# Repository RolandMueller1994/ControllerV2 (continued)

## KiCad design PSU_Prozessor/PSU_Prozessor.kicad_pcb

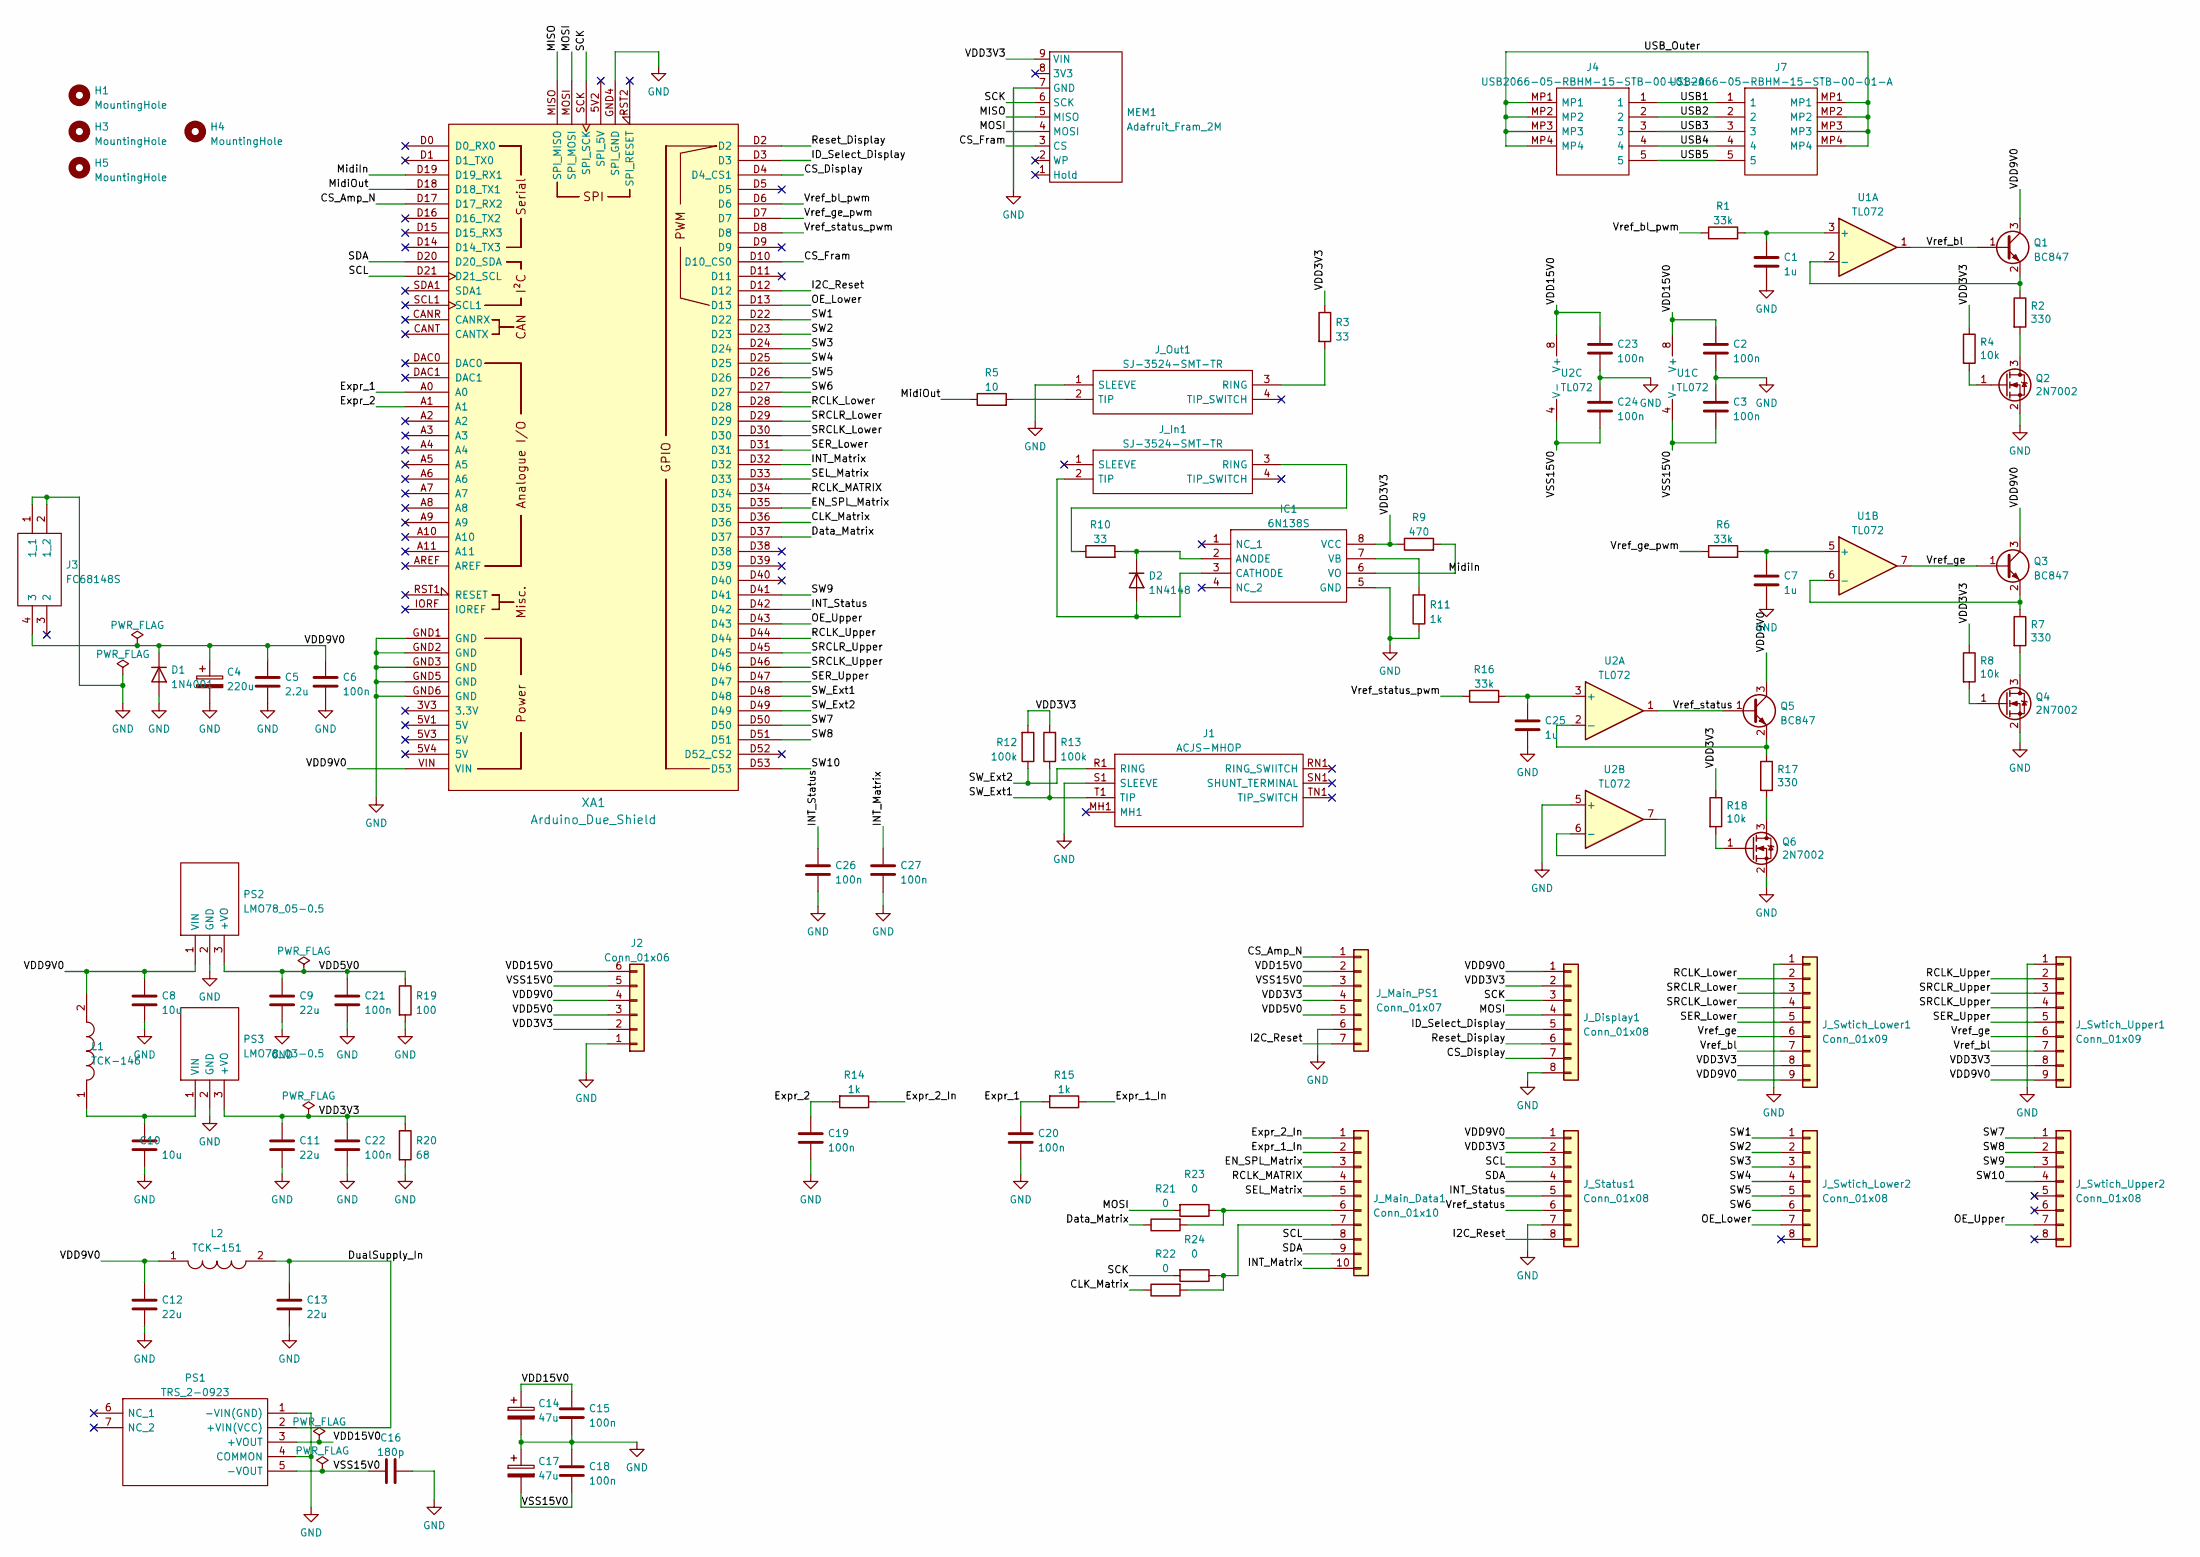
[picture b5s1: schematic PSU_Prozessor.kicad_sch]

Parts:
C1, C7, C25: 1u; C_1206_3216Metric_Pad1.33x1.80mm_HandSolder
C2, C3, C6, C15, C18, C19, C20, C21, C22, C23, C24, C26, C27: 100n; C_1206_3216Metric_Pad1.33x1.80mm_HandSolder
C4: 220u; CP_Elec_10x10
C5: 2.2u; C_1206_3216Metric_Pad1.33x1.80mm_HandSolder
C8, C10: 10u; C_1206_3216Metric_Pad1.33x1.80mm_HandSolder
C9, C11, C12, C13: 22u; C_1206_3216Metric_Pad1.33x1.80mm_HandSolder
C14, C17: 47u; CP_Elec_8x10.5
C16: 180p; C_1206_3216Metric_Pad1.33x1.80mm_HandSolder
D1: 1N4001; D_DO-41_SOD81_P10.16mm_Horizontal
D2: 1N4148; D_DO-35_SOD27_P7.62mm_Horizontal
H1, H3, H4, H5: MountingHole; MountingHole_4mm
IC1: 6N138S; SOP254P1016X460-8N; Manufacturer_Part_Number 6N138S; Mouser Part Number 859-6N138S
J1: ACJS-MHOP; ACJSMHOP; Manufacturer_Part_Number ACJS-MHOP; Mouser Part Number 523-ACJS-MHOP
J2: Conn_01x06; PinHeader_1x06_P2.54mm_Vertical
J3: FC68148S; FC68148S_2; Manufacturer_Part_Number FC68148S
J4, J7: USB2066-05-RBHM-15-STB-00-01-A; USB206605RBHM15STB0001A; Manufacturer_Part_Number USB2066-05-RBHM-15-STB-00-01-A; Mouser Part Number 640-2665RBHM15STB01A
J_Display1: Conn_01x08; JST_PH_B8B-PH-K_1x08_P2.00mm_Vertical
J_In1: SJ-3524-SMT-TR; Manufacturer_Part_Number SJ-3524-SMT-TR; Mouser Part Number 490-SJ-3524-SMT-TR
J_Main_Data1: Conn_01x10; JST_PH_B10B-PH-K_1x10_P2.00mm_Vertical
J_Main_PS1: Conn_01x07; JST_PH_B7B-PH-K_1x07_P2.00mm_Vertical
J_Out1: SJ-3524-SMT-TR; Manufacturer_Part_Number SJ-3524-SMT-TR; Mouser Part Number 490-SJ-3524-SMT-TR
J_Status1: Conn_01x08; JST_PH_B8B-PH-K_1x08_P2.00mm_Vertical
J_Swtich_Lower1: Conn_01x09; JST_PH_B9B-PH-K_1x09_P2.00mm_Vertical
J_Swtich_Lower2: Conn_01x08; JST_PH_B8B-PH-K_1x08_P2.00mm_Vertical
J_Swtich_Upper1: Conn_01x09; JST_PH_B9B-PH-K_1x09_P2.00mm_Vertical
J_Swtich_Upper2: Conn_01x08; JST_PH_B8B-PH-K_1x08_P2.00mm_Vertical
L1: TCK-146; TCK147; Manufacturer_Part_Number TCK-146; Mouser Part Number 495-TCK-146
L2: TCK-151; TCK151; Manufacturer_Part_Number TCK-151; Mouser Part Number 495-TCK-151
MEM1: Adafruit_Fram_2M; Adafruit_FRam_2M
PS1: TRS_2-0923; TRS20922; Manufacturer_Part_Number TRS 2-0923; Mouser Part Number 495-TRS2-0923
PS2: LMO78_05-0.5; LMO78_0505; Manufacturer_Part_Number LMO78_05-0.5
PS3: LMO78_03-0.5; LMO78_0505; Manufacturer_Part_Number LMO78_05-0.5
Q1, Q3, Q5: BC847; SOT-23
Q2, Q4, Q6: 2N7002; SOT-23
R1, R6, R16: 33k; R_1206_3216Metric_Pad1.30x1.75mm_HandSolder
R2, R7, R17: 330; R_1206_3216Metric_Pad1.30x1.75mm_HandSolder
R3, R10: 33; R_1206_3216Metric_Pad1.30x1.75mm_HandSolder
R4, R8, R18: 10k; R_1206_3216Metric_Pad1.30x1.75mm_HandSolder
R5: 10; R_1206_3216Metric_Pad1.30x1.75mm_HandSolder
R9: 470; R_1206_3216Metric_Pad1.30x1.75mm_HandSolder
R11, R14, R15: 1k; R_1206_3216Metric_Pad1.30x1.75mm_HandSolder
R12, R13: 100k; R_1206_3216Metric_Pad1.30x1.75mm_HandSolder
R19: 100; R_Axial_DIN0414_L11.9mm_D4.5mm_P15.24mm_Horizontal
R20: 68; R_Axial_DIN0414_L11.9mm_D4.5mm_P15.24mm_Horizontal
R21, R22, R23, R24: 0; R_1206_3216Metric_Pad1.30x1.75mm_HandSolder
U1, U2: TL072; SOIC127P600X175-8N
XA1: Arduino_Due_Shield

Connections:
/CLK_Matrix: R22.1, XA1.D36
/CS_Amp_N: J_Main_PS1.1, XA1.D17 (D17_RX2)
/CS_Display: J_Display1.7, XA1.D4 (D4_CS1)
/CS_Fram: MEM1.3 (CS), XA1.D10 (D10_CS0)
/Data_Matrix: R21.1, XA1.D37
/DualSupply_In: C13.1, L2.2, PS1.2 (+VIN(VCC))
/EN_SPL_Matrix: J_Main_Data1.3, XA1.D35
/Expr_1: C20.1, R15.2, XA1.A0
/Expr_1_In: J_Main_Data1.2, R15.1
/Expr_2: C19.1, R14.2, XA1.A1
/Expr_2_In: J_Main_Data1.1, R14.1
/I2C_Reset: J_Main_PS1.7, J_Status1.8, XA1.D12
/ID_Select_Display: J_Display1.5, XA1.D3
/INT_Matrix: C27.1, J_Main_Data1.10, XA1.D32
/INT_Status: C26.1, J_Status1.5, XA1.D42
/MISO: MEM1.5 (MISO), XA1.MISO (SPI_MISO)
/MOSI: J_Display1.4, MEM1.4 (MOSI), R23.2, XA1.MOSI (SPI_MOSI)
/MidiIn: IC1.6 (VO), R9.2, XA1.D19 (D19_RX1)
/MidiOut: R5.1, XA1.D18 (D18_TX1)
/OE_Lower: J_Swtich_Lower2.7, XA1.D13
/OE_Upper: J_Swtich_Upper2.7, XA1.D43
/RCLK_Lower: J_Swtich_Lower1.2, XA1.D28
/RCLK_MATRIX: J_Main_Data1.4, XA1.D34
/RCLK_Upper: J_Swtich_Upper1.2, XA1.D44
/Reset_Display: J_Display1.6, XA1.D2
/SCK: J_Display1.3, MEM1.6 (SCK), R24.2, XA1.SCK (SPI_SCK)
/SCL: J_Main_Data1.8, J_Status1.3, XA1.D21 (D21_SCL)
/SDA: J_Main_Data1.9, J_Status1.4, XA1.D20 (D20_SDA)
/SEL_Matrix: J_Main_Data1.5, XA1.D33
/SER_Lower: J_Swtich_Lower1.5, XA1.D31
/SER_Upper: J_Swtich_Upper1.5, XA1.D47
/SRCLK_Lower: J_Swtich_Lower1.4, XA1.D30
/SRCLK_Upper: J_Swtich_Upper1.4, XA1.D46
/SRCLR_Lower: J_Swtich_Lower1.3, XA1.D29
/SRCLR_Upper: J_Swtich_Upper1.3, XA1.D45
/SW1: J_Swtich_Lower2.1, XA1.D22
/SW2: J_Swtich_Lower2.2, XA1.D23
/SW3: J_Swtich_Lower2.3, XA1.D24
/SW4: J_Swtich_Lower2.4, XA1.D25
/SW5: J_Swtich_Lower2.5, XA1.D26
/SW6: J_Swtich_Lower2.6, XA1.D27
/SW7: J_Swtich_Upper2.1, XA1.D50
/SW8: J_Swtich_Upper2.2, XA1.D51
/SW9: J_Swtich_Upper2.3, XA1.D41
/SW10: J_Swtich_Upper2.4, XA1.D53
/SW_Ext1: J1.T1 (TIP), R13.1, XA1.D48
/SW_Ext2: J1.R1 (RING), R12.1, XA1.D49
/USB1: J4.1, J7.1
/USB2: J4.2, J7.2
/USB3: J4.3, J7.3
/USB4: J4.4, J7.4
/USB5: J4.5, J7.5
/USB_Outer: J4.MP1, J4.MP2, J4.MP3, J4.MP4, J7.MP1, J7.MP2, J7.MP3, J7.MP4
/VDD3V3: C11.1, C22.1, IC1.8 (VCC), J2.2, J_Display1.2, J_Main_PS1.4, J_Status1.2, J_Swtich_Lower1.8, J_Swtich_Upper1.8, MEM1.9 (VIN), PS3.3 (+VO), R3.1, R4.1, R8.1, R9.1, R12.2, R13.2, R18.1, R20.1
/VDD5V0: C9.1, C21.1, J2.3, J_Main_PS1.5, PS2.3 (+VO), R19.1
/VDD9V0: C4.1, C5.1, C6.1, C8.1, C12.1, D1.1 (K), J2.4, J3.4 (3), J_Display1.1, J_Status1.1, J_Swtich_Lower1.9, J_Swtich_Upper1.9, L1.2, L2.1, PS2.1 (VIN), Q1.3 (C), Q3.3 (C), Q5.3 (C), XA1.VIN
/VDD15V0: C2.1, C14.1, C15.1, C23.1, J2.6, J_Main_PS1.2, PS1.3 (+VOUT), U1.8 (V+), U2.8 (V+)
/VSS15V0: C3.2, C16.1, C17.2, C18.2, C24.2, J2.5, J_Main_PS1.3, PS1.5 (-VOUT), U1.4 (V-), U2.4 (V-)
/Vref_bl: J_Swtich_Lower1.7, J_Swtich_Upper1.7, Q1.1 (B), U1.1
/Vref_bl_pwm: R1.1, XA1.D6
/Vref_ge: J_Swtich_Lower1.6, J_Swtich_Upper1.6, Q3.1 (B), U1.7
/Vref_ge_pwm: R6.1, XA1.D7
/Vref_status: J_Status1.6, Q5.1 (B), U2.1
/Vref_status_pwm: R16.1, XA1.D8
GND: C1.2, C2.2, C3.1, C4.2, C5.2, C6.2, C7.2, C8.2, C9.2, C10.2, C11.2, C12.2, C13.2, C14.2, C15.2, C16.2, C17.1, C18.1, C19.2, C20.2, C21.2, C22.2, C23.2, C24.1, C25.2, C26.2, C27.2, D1.2 (A), IC1.5 (GND), J1.S1 (SLEEVE), J2.1, J3.1 (1_1), J3.2 (1_2), J_Display1.8, J_Main_PS1.6, J_Out1.1 (SLEEVE), J_Status1.7, J_Swtich_Lower1.1, J_Swtich_Upper1.1, MEM1.7 (GND), PS1.1 (-VIN(GND)), PS1.4 (COMMON), PS2.2 (GND), PS3.2 (GND), Q2.2 (S), Q4.2 (S), Q6.2 (S), R11.1, R19.2, R20.2, U2.5 (+), XA1.GND1 (GND), XA1.GND2 (GND), XA1.GND3 (GND), XA1.GND4 (SPI_GND), XA1.GND5 (GND), XA1.GND6 (GND)
unnamed: C1.1, R1.2, U1.3 (+)
unnamed: C7.1, R6.2, U1.5 (+)
unnamed: C10.1, L1.1, PS3.1 (VIN)
unnamed: C25.1, R16.2, U2.3 (+)
unnamed: D2.1 (K), IC1.2 (ANODE), R10.2
unnamed: D2.2 (A), IC1.3 (CATHODE), J_In1.2 (TIP)
unnamed: IC1.7 (VB), R11.2
unnamed: J_In1.3 (RING), R10.1
unnamed: J_Main_Data1.6, R21.2, R23.1
unnamed: J_Main_Data1.7, R22.2, R24.1
unnamed: J_Out1.2 (TIP), R5.2
unnamed: J_Out1.3 (RING), R3.2
unnamed: Q1.2 (E), R2.1, U1.2 (-)
unnamed: Q2.1 (G), R4.2
unnamed: Q2.3 (D), R2.2
unnamed: Q3.2 (E), R7.1, U1.6 (-)
unnamed: Q4.1 (G), R8.2
unnamed: Q4.3 (D), R7.2
unnamed: Q5.2 (E), R17.1, U2.2 (-)
unnamed: Q6.1 (G), R18.2
unnamed: Q6.3 (D), R17.2
unnamed: U2.6 (-), U2.7

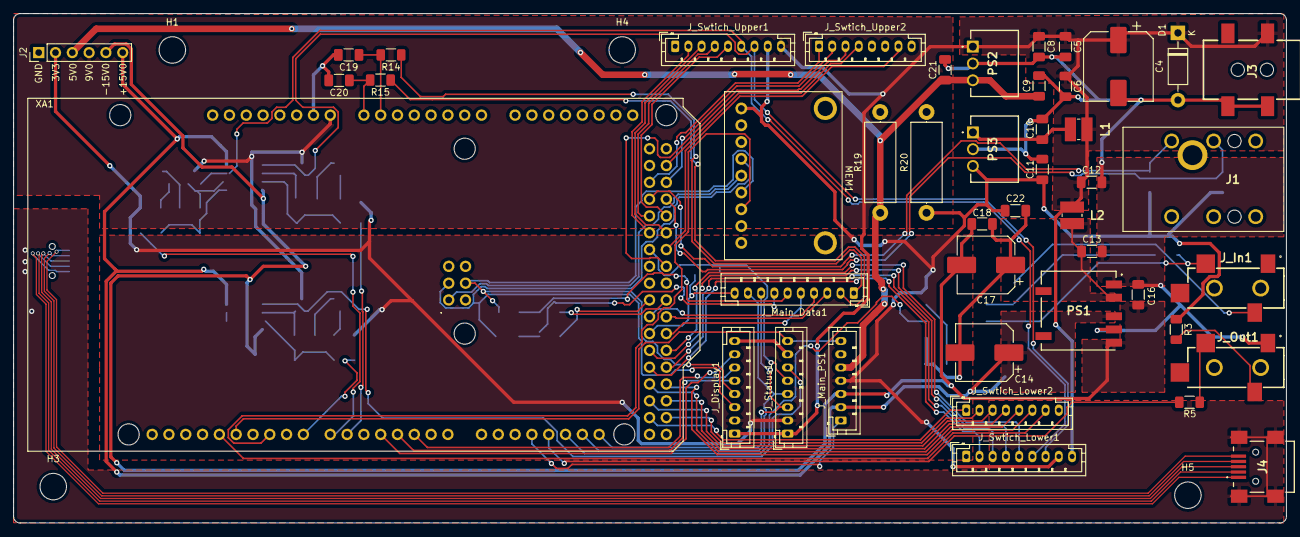
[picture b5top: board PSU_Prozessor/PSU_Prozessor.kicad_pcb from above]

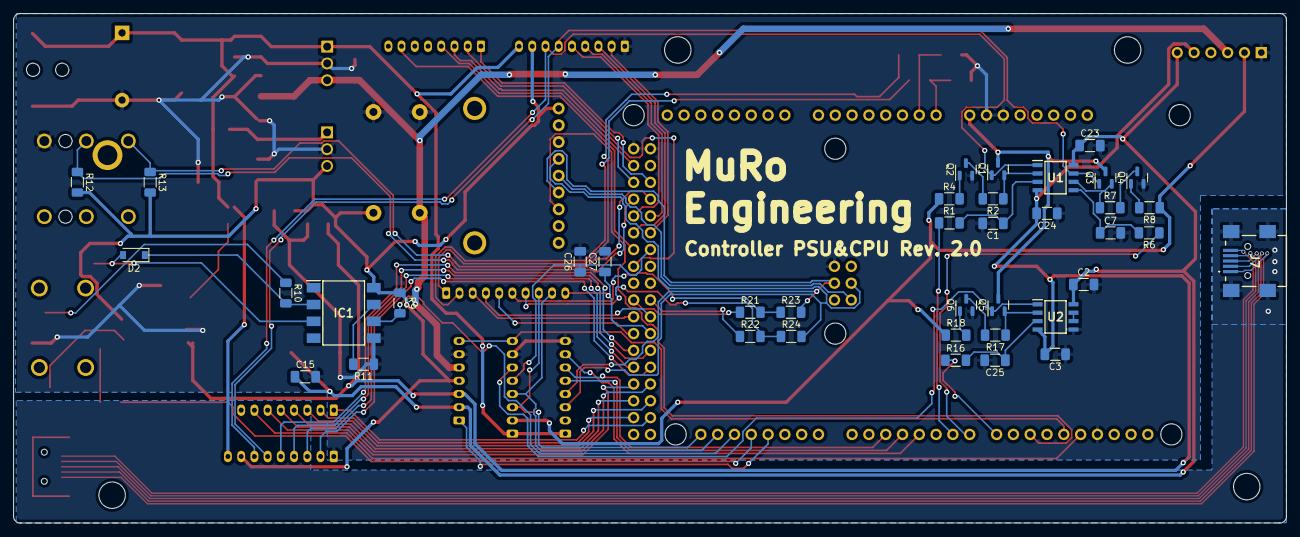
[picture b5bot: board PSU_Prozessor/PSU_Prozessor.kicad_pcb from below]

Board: 2 copper layers, 192.4 x 77.0 mm, 88 parts (39 on the bottom side), 87 nets.

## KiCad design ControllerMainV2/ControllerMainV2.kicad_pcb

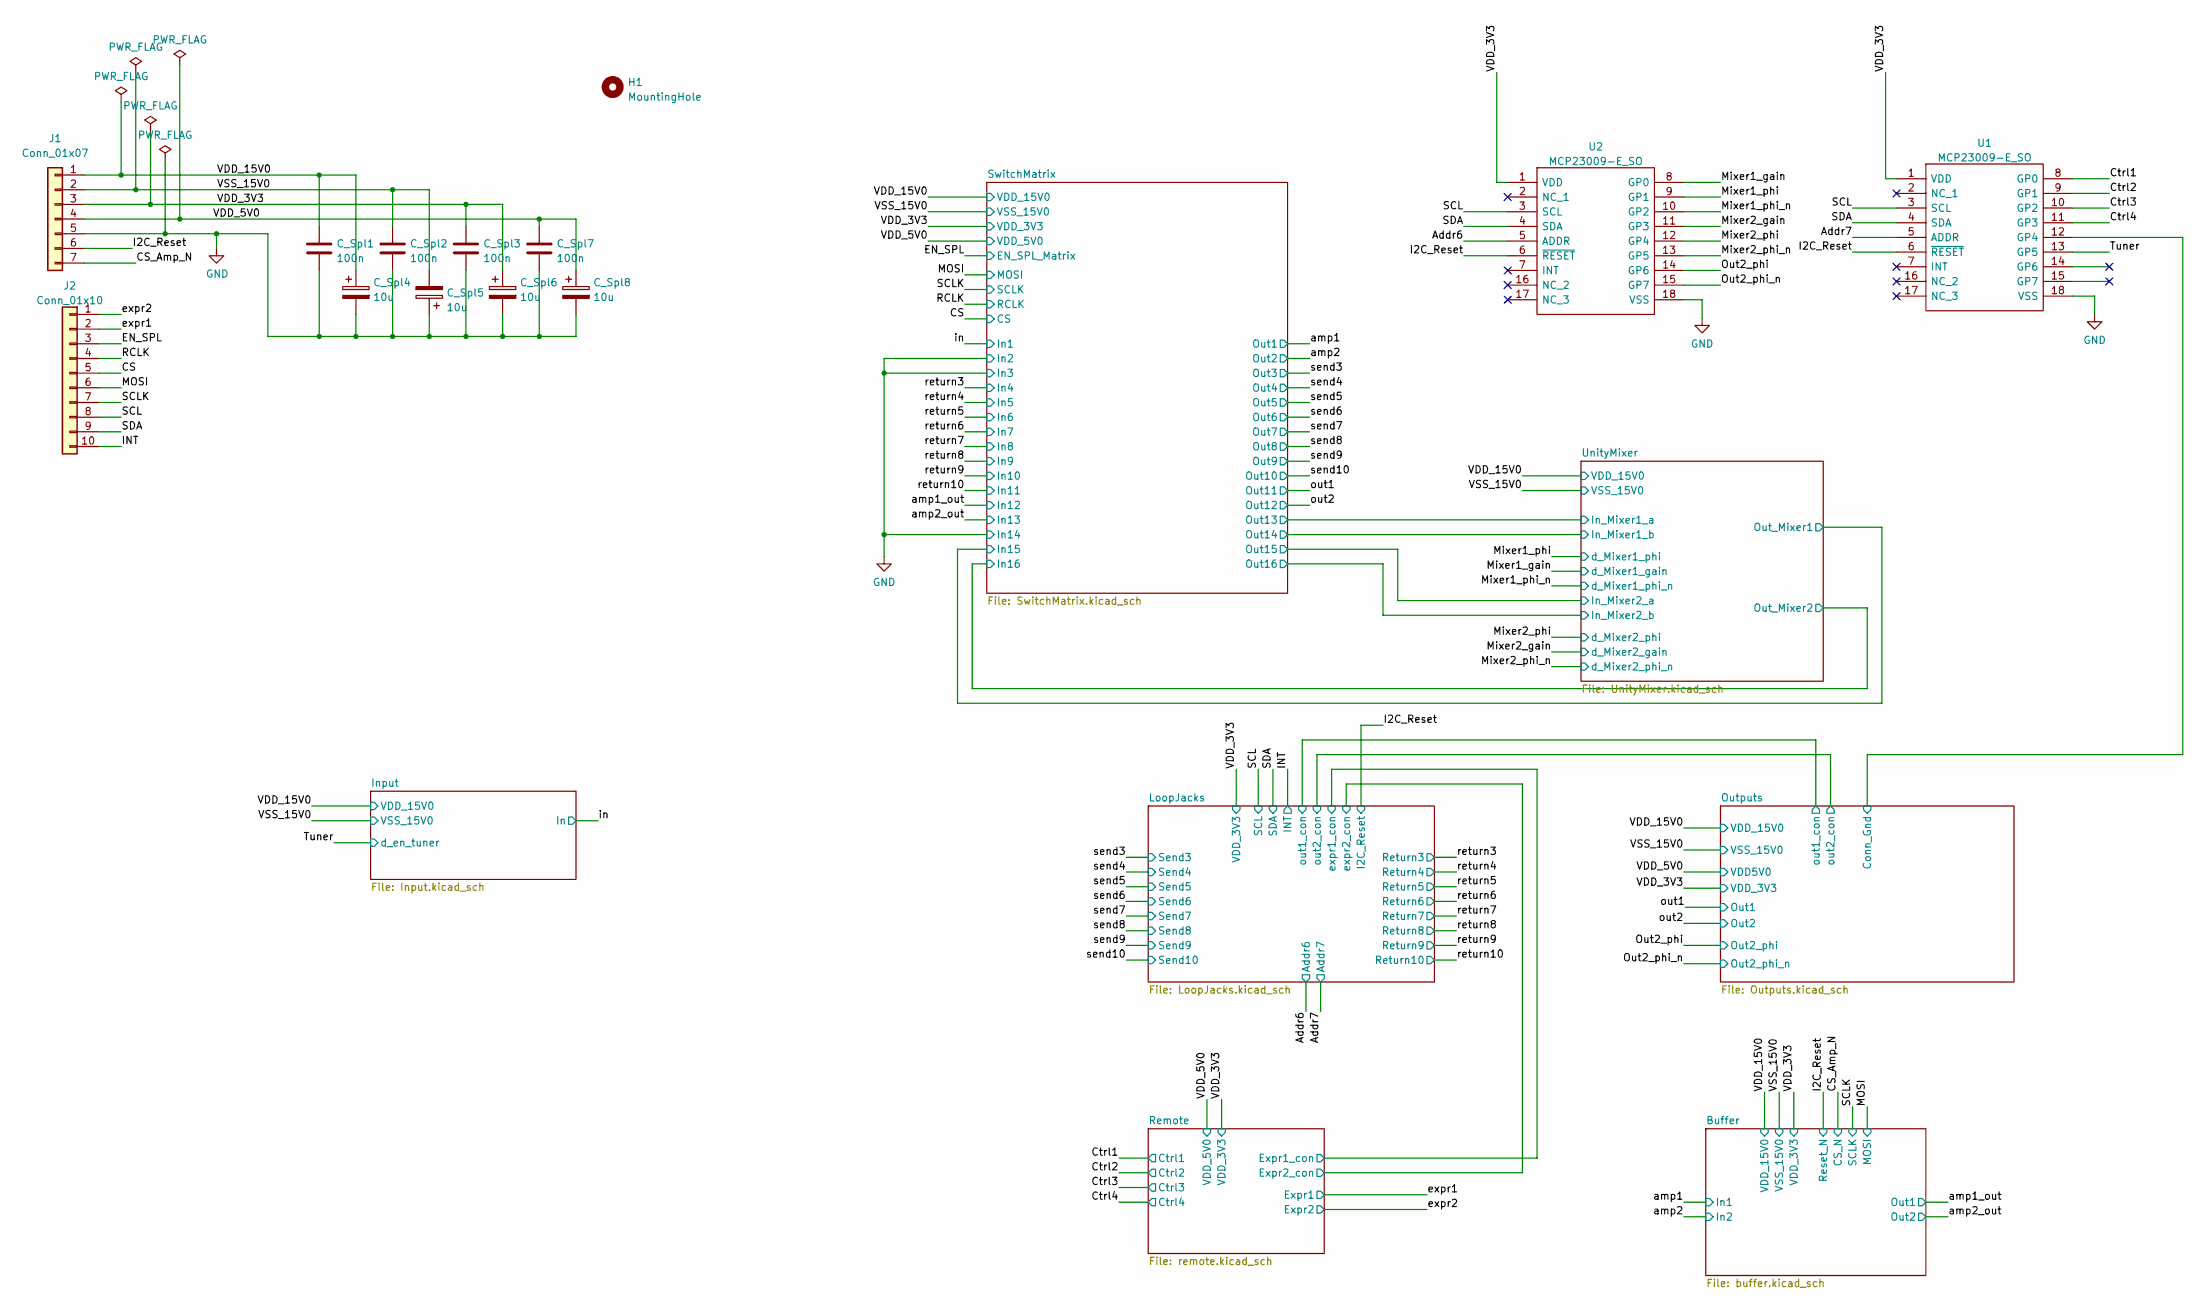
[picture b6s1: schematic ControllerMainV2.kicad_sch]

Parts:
C_Spl1, C_Spl2, C_Spl3, C_Spl7: 100n; C_1206_3216Metric_Pad1.33x1.80mm_HandSolder
C_Spl4, C_Spl5, C_Spl6, C_Spl8: 10u; C_Elec_4x5.4
H1: MountingHole; MountingHole_3.2mm_M3
J1: Conn_01x07
J2: Conn_01x10; JST_PH_B10B-PH-K_1x10_P2.00mm_Vertical
U1, U2: MCP23009-E_SO; SOIC127P1030X265-18N; Manufacturer_Part_Number MCP23009-E/SO; Mouser Part Number 579-MCP23009-E/SO

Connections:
/Addr6: U2.5 (ADDR); also elsewhere on the board
/Addr7: U1.5 (ADDR); also elsewhere on the board
/CS: J2.5; also elsewhere on the board
/Ctrl1: U1.8 (GP0); also elsewhere on the board
/Ctrl2: U1.9 (GP1); also elsewhere on the board
/Ctrl3: U1.10 (GP2); also elsewhere on the board
/Ctrl4: U1.11 (GP3); also elsewhere on the board
/EN_SPL: J2.3; also elsewhere on the board
/INT: J2.10; also elsewhere on the board
/MOSI: J2.6; also elsewhere on the board
/Mixer1_gain: U2.8 (GP0); also elsewhere on the board
/Mixer1_phi: U2.9 (GP1); also elsewhere on the board
/Mixer1_phi_n: U2.10 (GP2); also elsewhere on the board
/Mixer2_gain: U2.11 (GP3); also elsewhere on the board
/Mixer2_phi: U2.12 (GP4); also elsewhere on the board
/Mixer2_phi_n: U2.13 (GP5); also elsewhere on the board
/Out2_phi: U2.14 (GP6); also elsewhere on the board
/Out2_phi_n: U2.15 (GP7); also elsewhere on the board
/Outputs/Conn_Gnd: U1.12 (GP4); also elsewhere on the board
/RCLK: J2.4; also elsewhere on the board
/SCL: J2.8, U1.3 (SCL), U2.3 (SCL); also elsewhere on the board
/SCLK: J2.7; also elsewhere on the board
/SDA: J2.9, U1.4 (SDA), U2.4 (SDA); also elsewhere on the board
/Tuner: U1.13 (GP5); also elsewhere on the board
/expr1: J2.2; also elsewhere on the board
/expr2: J2.1; also elsewhere on the board

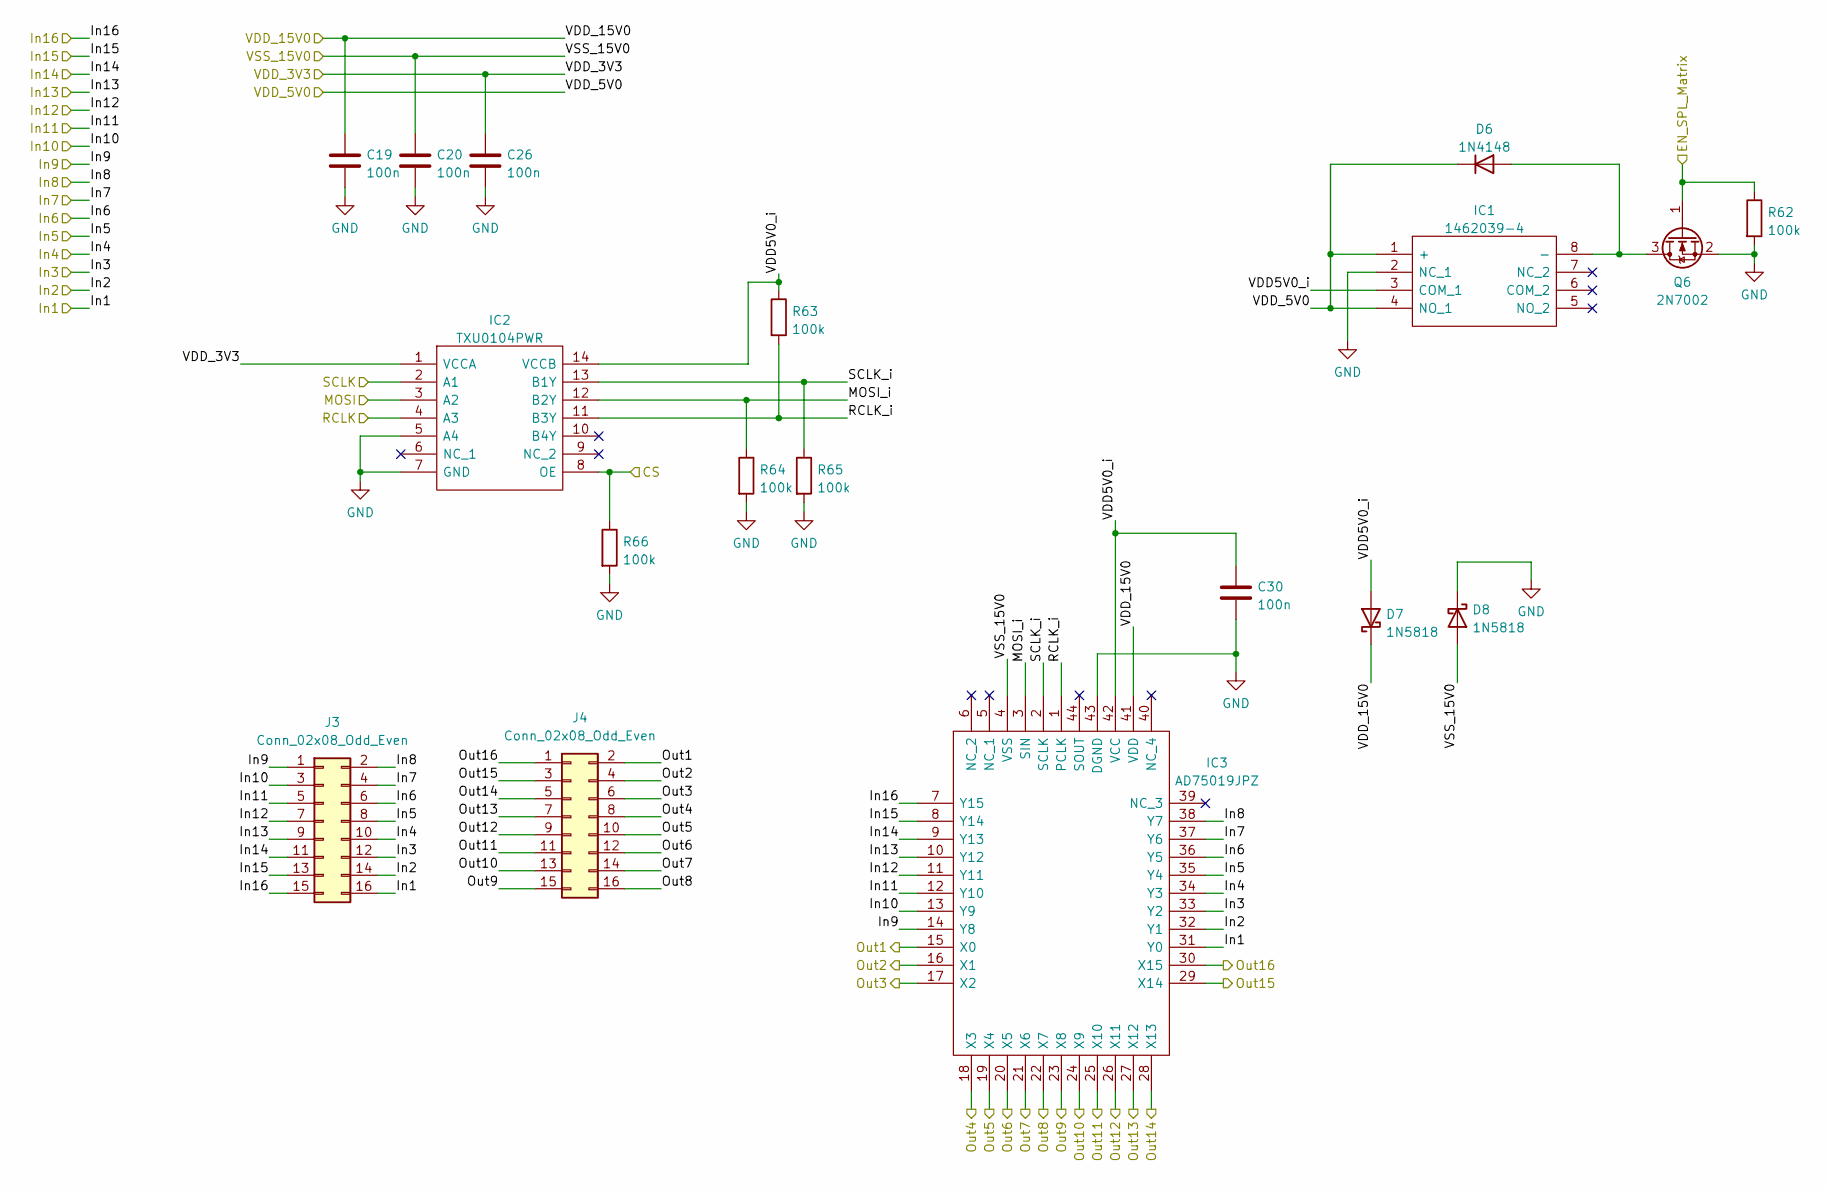
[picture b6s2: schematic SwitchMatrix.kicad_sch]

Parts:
C19, C20, C26, C30: 100n; C_1206_3216Metric_Pad1.33x1.80mm_HandSolder
D6: 1N4148; D_SOD-123
D7, D8: 1N5818; D_SOD-123
IC1: 1462039-4; 14620394; Manufacturer_Part_Number 1462039-4; Mouser Part Number 655-1462039-4
IC2: TXU0104PWR; SOP65P640X120-14N; Manufacturer_Part_Number TXU0104PWR; Mouser Part Number 595-TXU0104PWR
IC3: AD75019JPZ; 69802144LF; Manufacturer_Part_Number AD75019JPZ; Mouser Part Number 584-AD75019JPZ
J3, J4: Conn_02x08_Odd_Even; PinHeader_2x08_P1.27mm_Vertical_SMD
Q6: 2N7002; SOT-23
R62, R63, R64, R65, R66: 100k; R_1206_3216Metric_Pad1.30x1.75mm_HandSolder

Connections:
/CS: IC2.8 (OE), R66.1; also elsewhere on the board
/EN_SPL: Q6.1 (G), R62.1; also elsewhere on the board
/MOSI: IC2.3 (A2); also elsewhere on the board
/RCLK: IC2.4 (A3); also elsewhere on the board
/SCLK: IC2.2 (A1); also elsewhere on the board
/SwitchMatrix/In15: IC3.8 (Y14), J3.13; also elsewhere on the board
/SwitchMatrix/In16: IC3.7 (Y15), J3.15; also elsewhere on the board
/SwitchMatrix/MOSI_i: IC2.12 (B2Y), IC3.3 (SIN), R64.1
/SwitchMatrix/Out13: IC3.27 (X12), J4.7; also elsewhere on the board
/SwitchMatrix/Out14: IC3.28 (X13), J4.5; also elsewhere on the board
/SwitchMatrix/Out15: IC3.29 (X14), J4.3; also elsewhere on the board
/SwitchMatrix/Out16: IC3.30 (X15), J4.1; also elsewhere on the board
/SwitchMatrix/RCLK_i: IC2.11 (B3Y), IC3.1 (PCLK), R63.2
/SwitchMatrix/SCLK_i: IC2.13 (B1Y), IC3.2 (SCLK), R65.1
/SwitchMatrix/VDD5V0_i: C30.1, D7.2 (A), IC1.3 (COM_1), IC2.14 (VCCB), IC3.42 (VCC), R63.1
/amp1: IC3.15 (X0), J4.2; also elsewhere on the board
/amp1_out: IC3.32 (Y1), J3.14; also elsewhere on the board
/amp2: IC3.16 (X1), J4.4; also elsewhere on the board
/amp2_out: IC3.33 (Y2), J3.12; also elsewhere on the board
/in: IC3.31 (Y0), J3.16; also elsewhere on the board
/out1: IC3.25 (X10), J4.11; also elsewhere on the board
/out2: IC3.26 (X11), J4.9; also elsewhere on the board
/return3: IC3.34 (Y3), J3.10; also elsewhere on the board
/return4: IC3.35 (Y4), J3.8; also elsewhere on the board
/return5: IC3.36 (Y5), J3.6; also elsewhere on the board
/return6: IC3.37 (Y6), J3.4; also elsewhere on the board
/return7: IC3.38 (Y7), J3.2; also elsewhere on the board
/return8: IC3.14 (Y8), J3.1; also elsewhere on the board
/return9: IC3.13 (Y9), J3.3; also elsewhere on the board
/return10: IC3.12 (Y10), J3.5; also elsewhere on the board
/send3: IC3.17 (X2), J4.6; also elsewhere on the board
/send4: IC3.18 (X3), J4.8; also elsewhere on the board
/send5: IC3.19 (X4), J4.10; also elsewhere on the board
/send6: IC3.20 (X5), J4.12; also elsewhere on the board
/send7: IC3.21 (X6), J4.14; also elsewhere on the board
/send8: IC3.22 (X7), J4.16; also elsewhere on the board
/send9: IC3.23 (X8), J4.15; also elsewhere on the board
/send10: IC3.24 (X9), J4.13; also elsewhere on the board
unnamed: D6.2 (A), IC1.8 (-), Q6.3 (D)

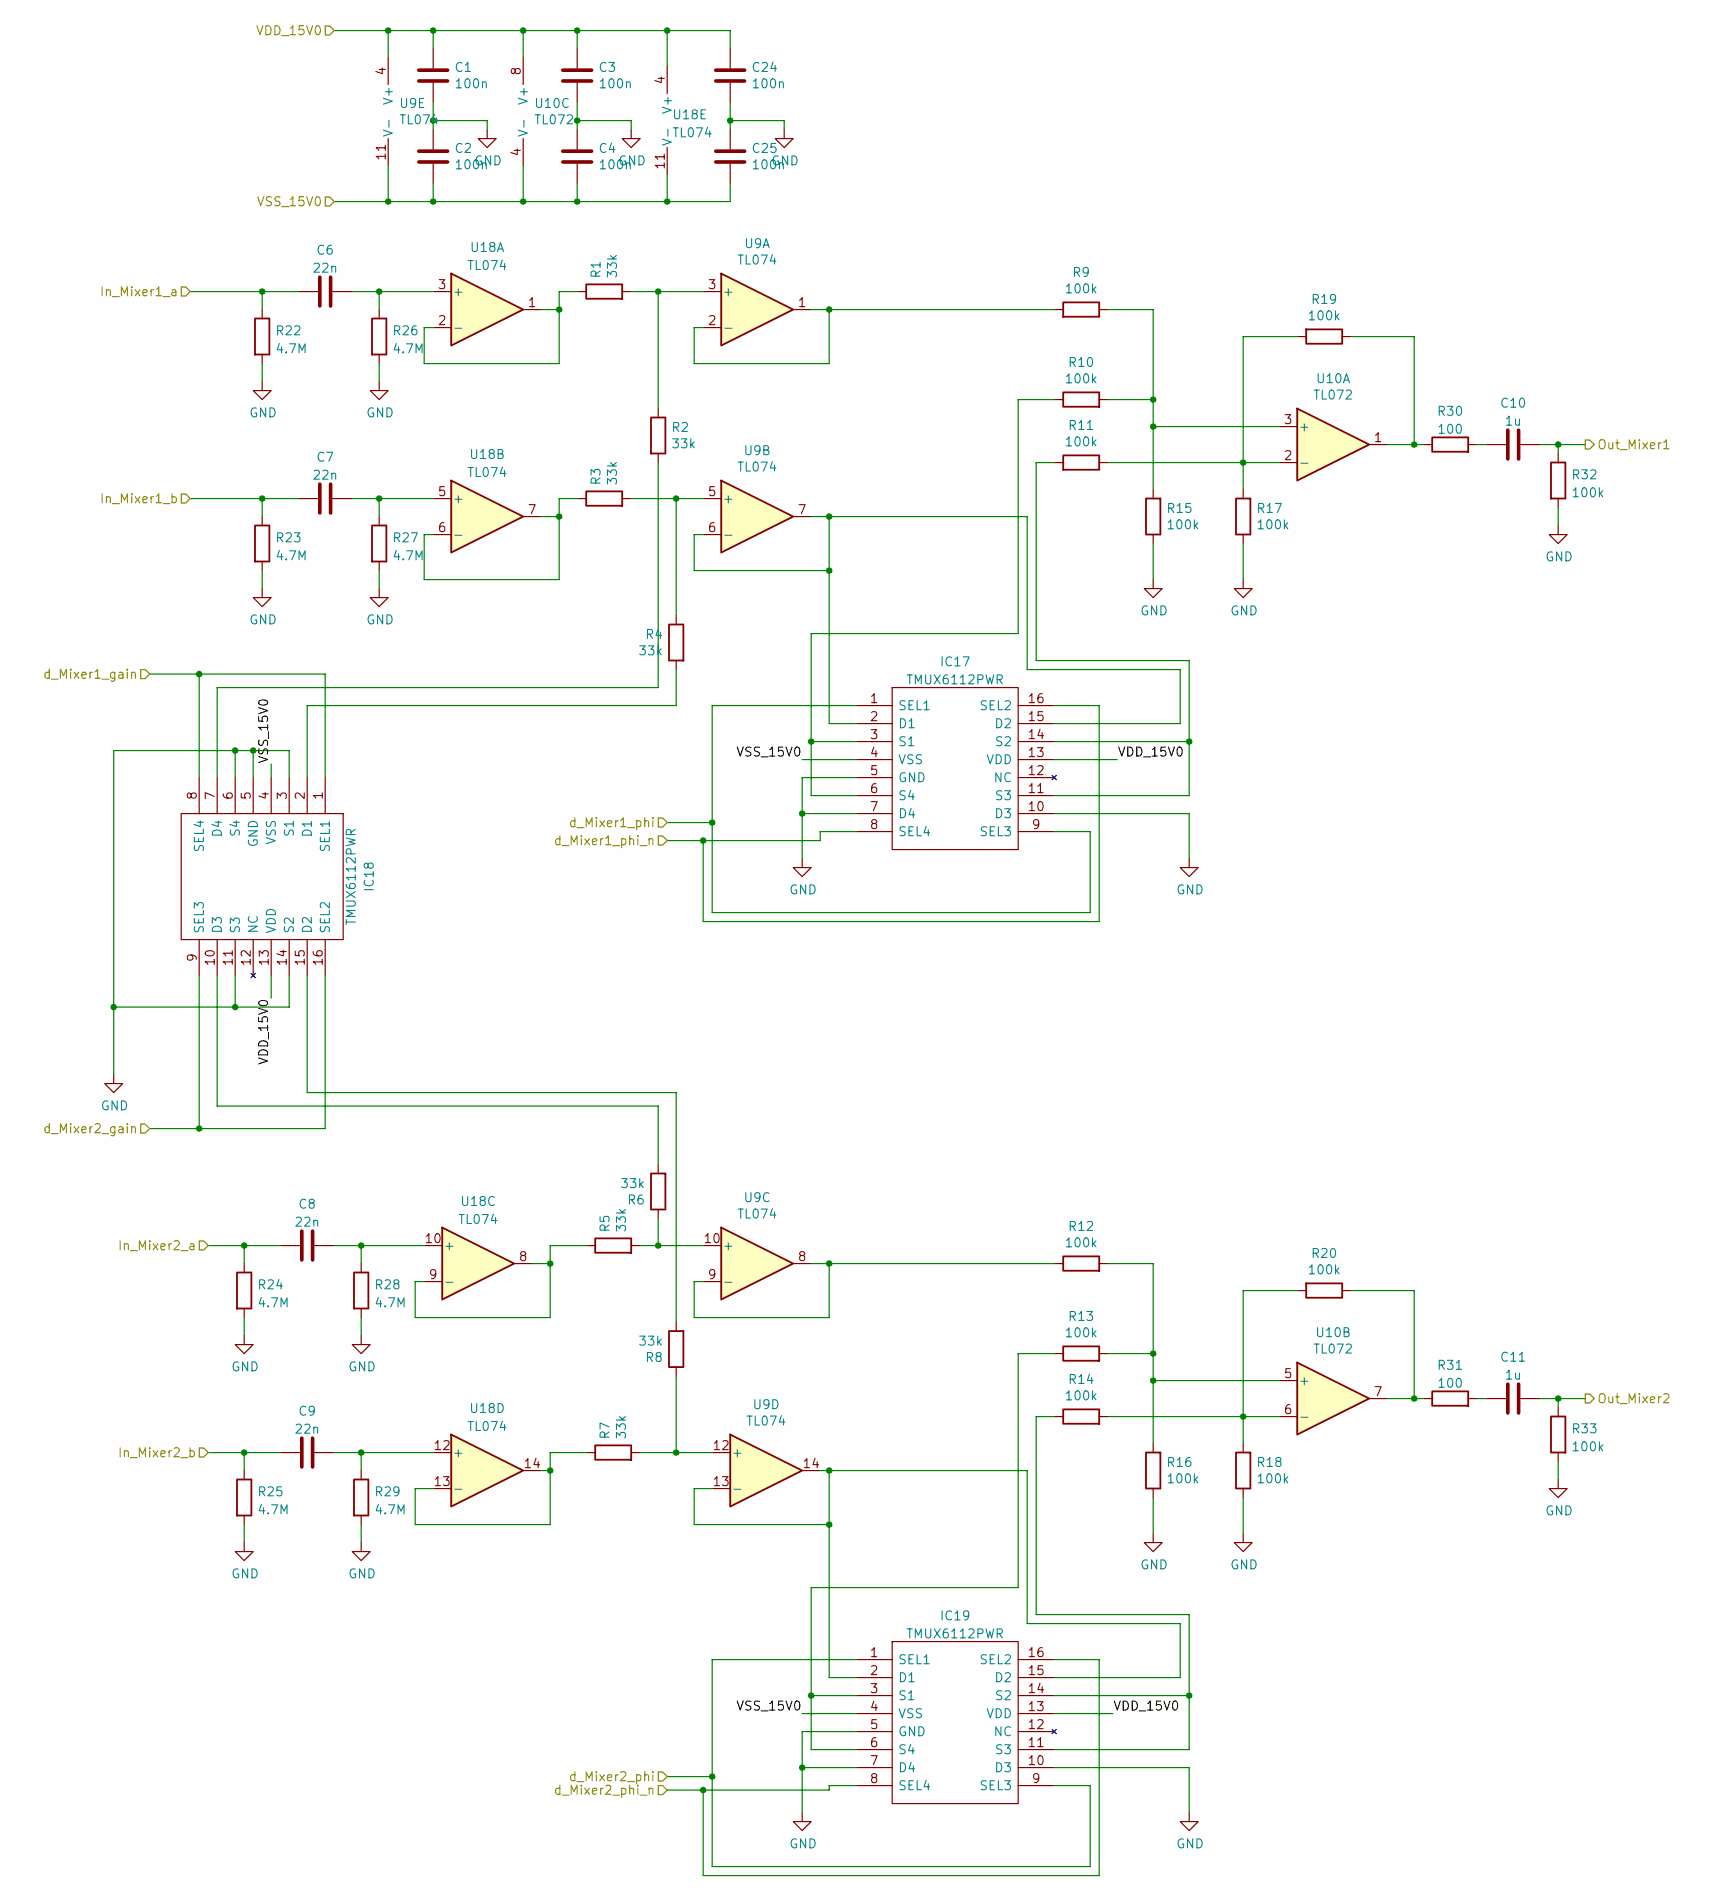
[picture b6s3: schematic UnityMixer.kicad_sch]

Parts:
C1, C2, C3, C4, C24, C25: 100n; C_1206_3216Metric_Pad1.33x1.80mm_HandSolder
C6, C7, C8, C9: 22n; C_1206_3216Metric_Pad1.33x1.80mm_HandSolder
C10, C11: 1u; C_1206_3216Metric_Pad1.33x1.80mm_HandSolder
IC17, IC18, IC19: TMUX6112PWR; SOP65P640X120-16N; Manufacturer_Part_Number TMUX6112PWR; Mouser Part Number 595-TMUX6112PWR
R1, R2, R3, R4, R5, R6, R7, R8: 33k; R_1206_3216Metric_Pad1.30x1.75mm_HandSolder
R9, R10, R11, R12, R13, R14, R15, R16, R17, R18, R19, R20, R32, R33: 100k; R_1206_3216Metric_Pad1.30x1.75mm_HandSolder
R22, R23, R24, R25, R26, R27, R28, R29: 4.7M; R_1206_3216Metric_Pad1.30x1.75mm_HandSolder
R30, R31: 100; R_1206_3216Metric_Pad1.30x1.75mm_HandSolder
U9, U18: TL074; SOIC127P600X175-14N
U10: TL072; SOIC127P600X175-8N

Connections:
/Mixer1_gain: IC18.1 (SEL1), IC18.8 (SEL4); also elsewhere on the board
/Mixer1_phi: IC17.1 (SEL1), IC17.9 (SEL3); also elsewhere on the board
/Mixer1_phi_n: IC17.8 (SEL4), IC17.16 (SEL2); also elsewhere on the board
/Mixer2_gain: IC18.9 (SEL3), IC18.16 (SEL2); also elsewhere on the board
/Mixer2_phi: IC19.1 (SEL1), IC19.9 (SEL3); also elsewhere on the board
/Mixer2_phi_n: IC19.8 (SEL4), IC19.16 (SEL2); also elsewhere on the board
/SwitchMatrix/In15: C10.2, R32.1; also elsewhere on the board
/SwitchMatrix/In16: C11.2, R33.1; also elsewhere on the board
/SwitchMatrix/Out13: C6.1, R22.1; also elsewhere on the board
/SwitchMatrix/Out14: C7.1, R23.1; also elsewhere on the board
/SwitchMatrix/Out15: C8.1, R24.1; also elsewhere on the board
/SwitchMatrix/Out16: C9.1, R25.1; also elsewhere on the board
unnamed: C6.2, R26.1, U18.3 (+)
unnamed: C7.2, R27.1, U18.5 (+)
unnamed: C8.2, R28.1, U18.10 (+)
unnamed: C9.2, R29.1, U18.12 (+)
unnamed: C10.1, R30.2
unnamed: C11.1, R31.2
unnamed: IC17.3 (S1), IC17.6 (S4), R10.1
unnamed: IC17.11 (S3), IC17.14 (S2), R11.2
unnamed: IC17.2 (D1), IC17.15 (D2), U9.6 (-), U9.7
unnamed: IC18.2 (D1), R4.2
unnamed: IC18.7 (D4), R2.2
unnamed: IC18.10 (D3), R6.2
unnamed: IC18.15 (D2), R8.2
unnamed: IC19.3 (S1), IC19.6 (S4), R13.1
unnamed: IC19.11 (S3), IC19.14 (S2), R14.1
unnamed: IC19.2 (D1), IC19.15 (D2), U9.13 (-), U9.14
unnamed: R1.1, U18.1, U18.2 (-)
unnamed: R1.2, R2.1, U9.3 (+)
unnamed: R3.1, U18.6 (-), U18.7
unnamed: R3.2, R4.1, U9.5 (+)
unnamed: R5.1, U18.8, U18.9 (-)
unnamed: R5.2, R6.1, U9.10 (+)
unnamed: R7.1, U18.13 (-), U18.14
unnamed: R7.2, R8.1, U9.12 (+)
unnamed: R9.2, U9.1, U9.2 (-)
unnamed: R9.1, R10.2, R15.2, U10.3 (+)
unnamed: R11.1, R17.2, R19.2, U10.2 (-)
unnamed: R12.1, U9.8, U9.9 (-)
unnamed: R12.2, R13.2, R16.2, U10.5 (+)
unnamed: R14.2, R18.2, R20.2, U10.6 (-)
unnamed: R19.1, R30.1, U10.1
unnamed: R20.1, R31.1, U10.7
